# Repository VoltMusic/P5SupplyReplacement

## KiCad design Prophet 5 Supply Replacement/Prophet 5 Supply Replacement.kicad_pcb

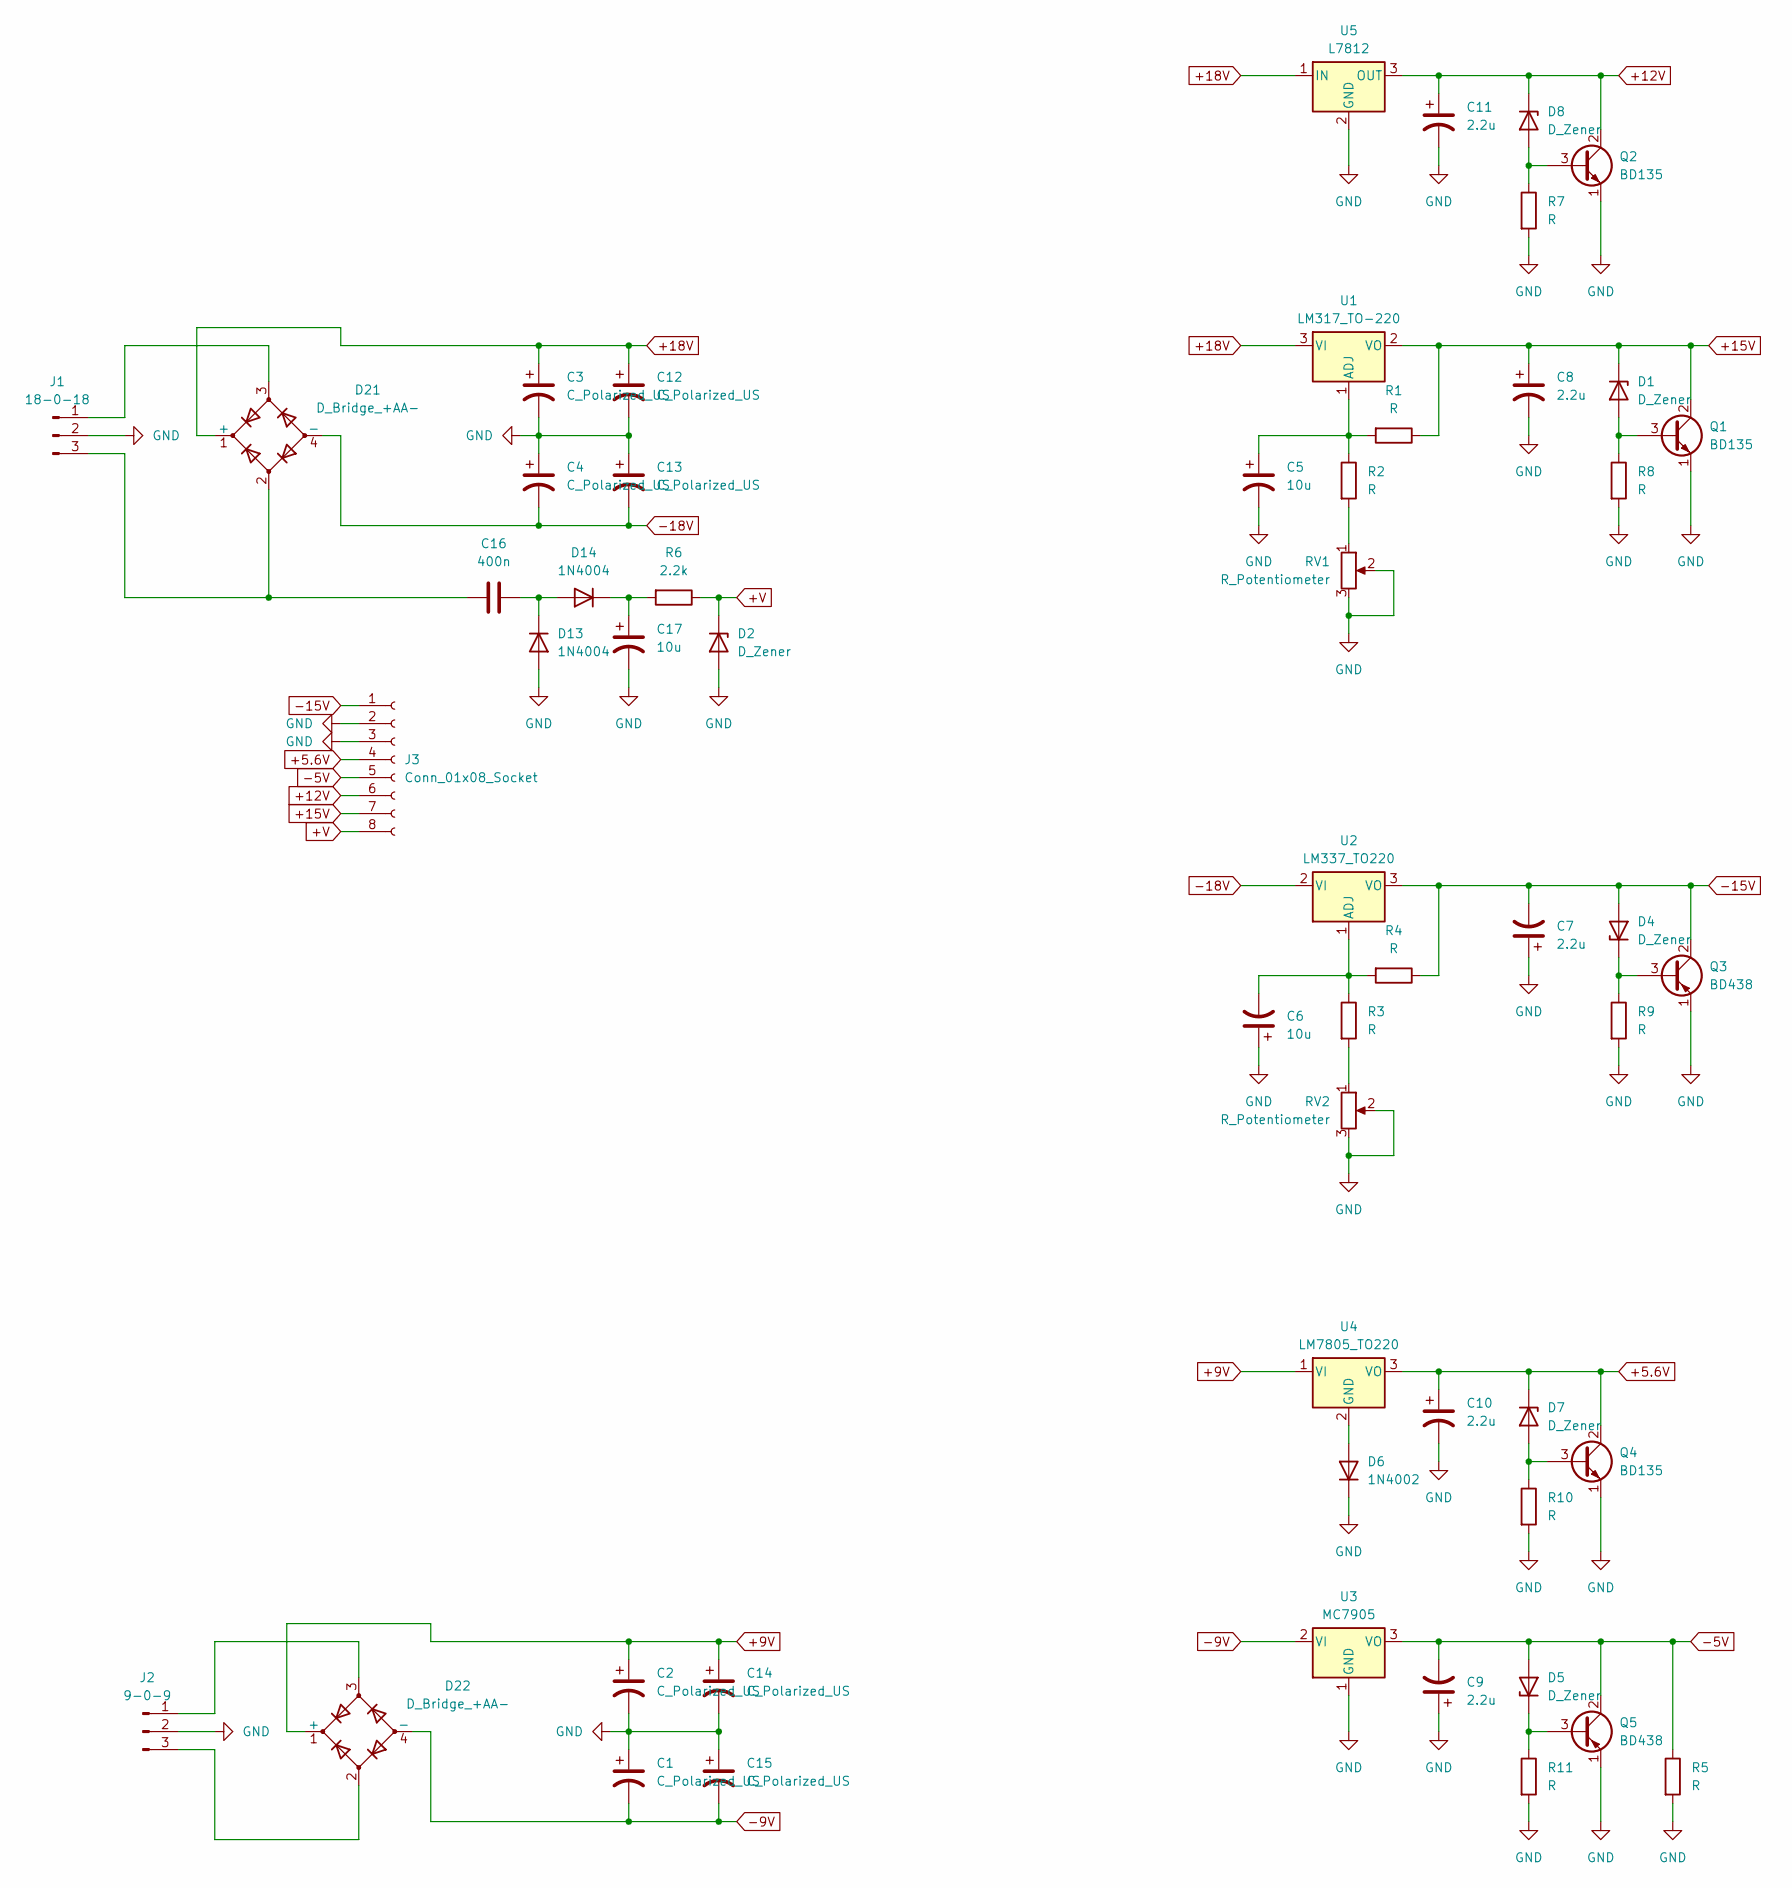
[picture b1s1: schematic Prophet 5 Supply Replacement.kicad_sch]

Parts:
C1, C2, C3, C4, C12, C13, C14, C15: C_Polarized_US; CP_Radial_D16.0mm_P7.50mm
C5, C6, C17: 10u; CP_Radial_D6.3mm_P2.50mm
C7, C8, C9, C10, C11: 2.2u; CP_Radial_D6.3mm_P2.50mm
C16: 400n; C_Disc_D7.5mm_W2.5mm_P5.00mm
D1, D2, D4, D5, D7, D8: D_Zener; D_DO-35_SOD27_P10.16mm_Horizontal
D6: 1N4002; D_DO-41_SOD81_P10.16mm_Horizontal
D13, D14: 1N4004; D_DO-41_SOD81_P10.16mm_Horizontal
D21, D22: D_Bridge_+AA-; Diode_Bridge_Vishay_GBU
J1: 18-0-18; Molex_KK-396_5273-03A_1x03_P3.96mm_Vertical
J2: 9-0-9; Molex_KK-396_5273-03A_1x03_P3.96mm_Vertical
J3: Conn_01x08_Socket; Molex_KK-396_5273-08A_1x08_P3.96mm_Vertical
Q1, Q2, Q4: BD135; TO-126-3_Vertical
Q3, Q5: BD438; TO-126-3_Vertical
R1, R2, R3, R4, R5, R7, R8, R9, R10, R11: R; R_Axial_DIN0207_L6.3mm_D2.5mm_P10.16mm_Horizontal
R6: 2.2k; R_Axial_DIN0207_L6.3mm_D2.5mm_P10.16mm_Horizontal
RV1, RV2: R_Potentiometer; Potentiometer_Bourns_3386F_Vertical
U1: LM317_TO-220; TO-220-3_Vertical
U2: LM337_TO220; TO-220-3_Vertical
U3: MC7905; TO-220-3_Horizontal_TabDown
U4: LM7805_TO220; TO-220-3_Vertical
U5: L7812; TO-220-3_Horizontal_TabDown

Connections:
+5.6V: C10.1, D7.1 (K), J3.4, Q4.2 (C), U4.3 (VO)
+9V: C2.1, C14.1, D22.1 (+), U4.1 (VI)
+12V: C11.1, D8.1 (K), J3.6, Q2.2 (C), U5.3 (OUT)
+15V: C8.1, D1.1 (K), J3.7, Q1.2 (C), R1.1, U1.2 (VO)
+18V: C3.1, C12.1, D21.1 (+), U1.3 (VI), U5.1 (IN)
+V: D2.1 (K), J3.8, R6.1
-5V: C9.2, D5.2 (A), J3.5, Q5.2 (C), R5.1, U3.3 (VO)
-9V: C1.2, C15.2, D22.4 (-), U3.2 (VI)
-15V: C7.2, D4.2 (A), J3.1, Q3.2 (C), R4.1, U2.3 (VO)
-18V: C4.2, C13.2, D21.4 (-), U2.2 (VI)
GND: C1.1, C2.2, C3.2, C4.1, C5.2, C6.1, C7.1, C8.2, C9.1, C10.2, C11.2, C12.2, C13.1, C14.2, C15.1, C17.2, D2.2 (A), D6.1 (K), D13.2 (A), J1.2, J2.2, J3.2, J3.3, Q1.1 (E), Q2.1 (E), Q3.1 (E), Q4.1 (E), Q5.1 (E), R5.2, R7.2, R8.2, R9.2, R10.2, R11.2, RV1.2, RV1.3, RV2.2, RV2.3, U3.1 (GND), U5.2 (GND)
unnamed: D1.2 (A), Q1.3 (B), R8.1
unnamed: D4.1 (K), Q3.3 (B), R9.1
unnamed: D5.1 (K), Q5.3 (B), R11.1
unnamed: D6.2 (A), U4.2 (GND)
unnamed: D7.2 (A), Q4.3 (B), R10.1
unnamed: D8.2 (A), Q2.3 (B), R7.1
unnamed: C16.2, D13.1 (K), D14.2 (A)
unnamed: C17.1, D14.1 (K), R6.2
unnamed: D21.3, J1.1
unnamed: C16.1, D21.2, J1.3
unnamed: D22.3, J2.1
unnamed: D22.2, J2.3
unnamed: R2.2, RV1.1
unnamed: R3.2, RV2.1
unnamed: C5.1, R1.2, R2.1, U1.1 (ADJ)
unnamed: C6.2, R3.1, R4.2, U2.1 (ADJ)

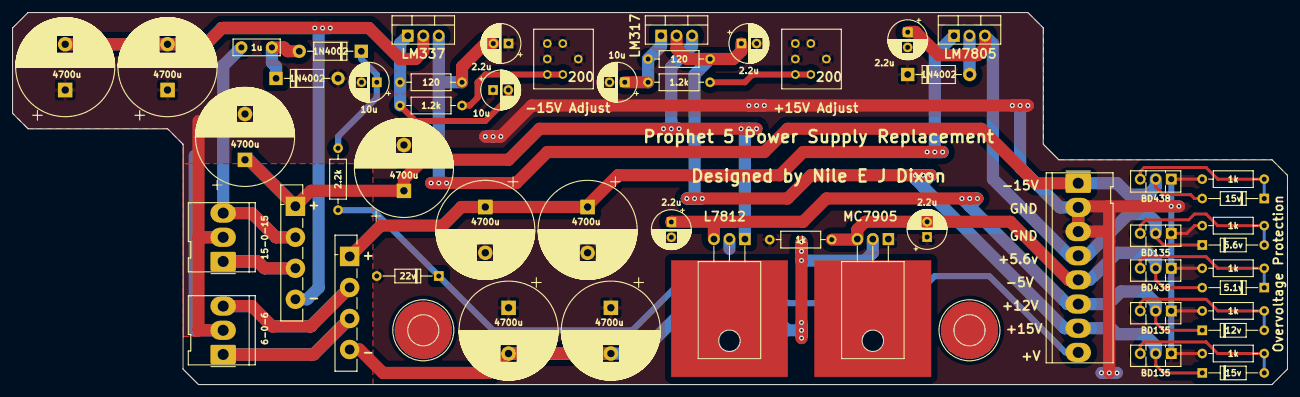
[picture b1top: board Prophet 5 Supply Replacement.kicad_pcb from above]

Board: 2 copper layers, 208.9 x 61.0 mm, 54 parts (0 on the bottom side), 27 nets.
